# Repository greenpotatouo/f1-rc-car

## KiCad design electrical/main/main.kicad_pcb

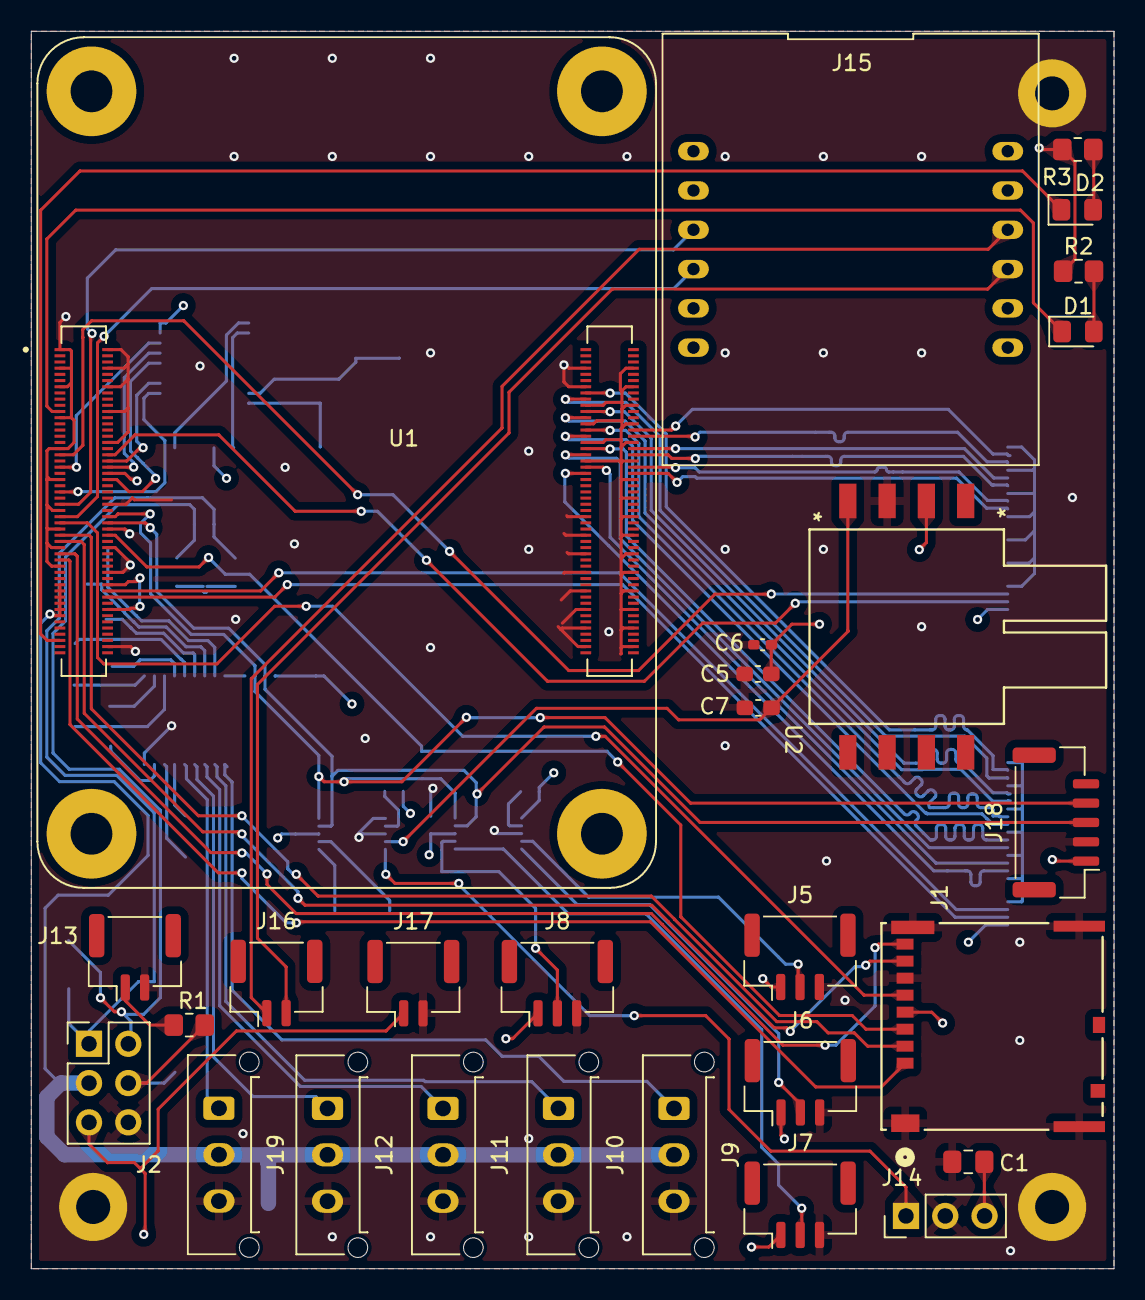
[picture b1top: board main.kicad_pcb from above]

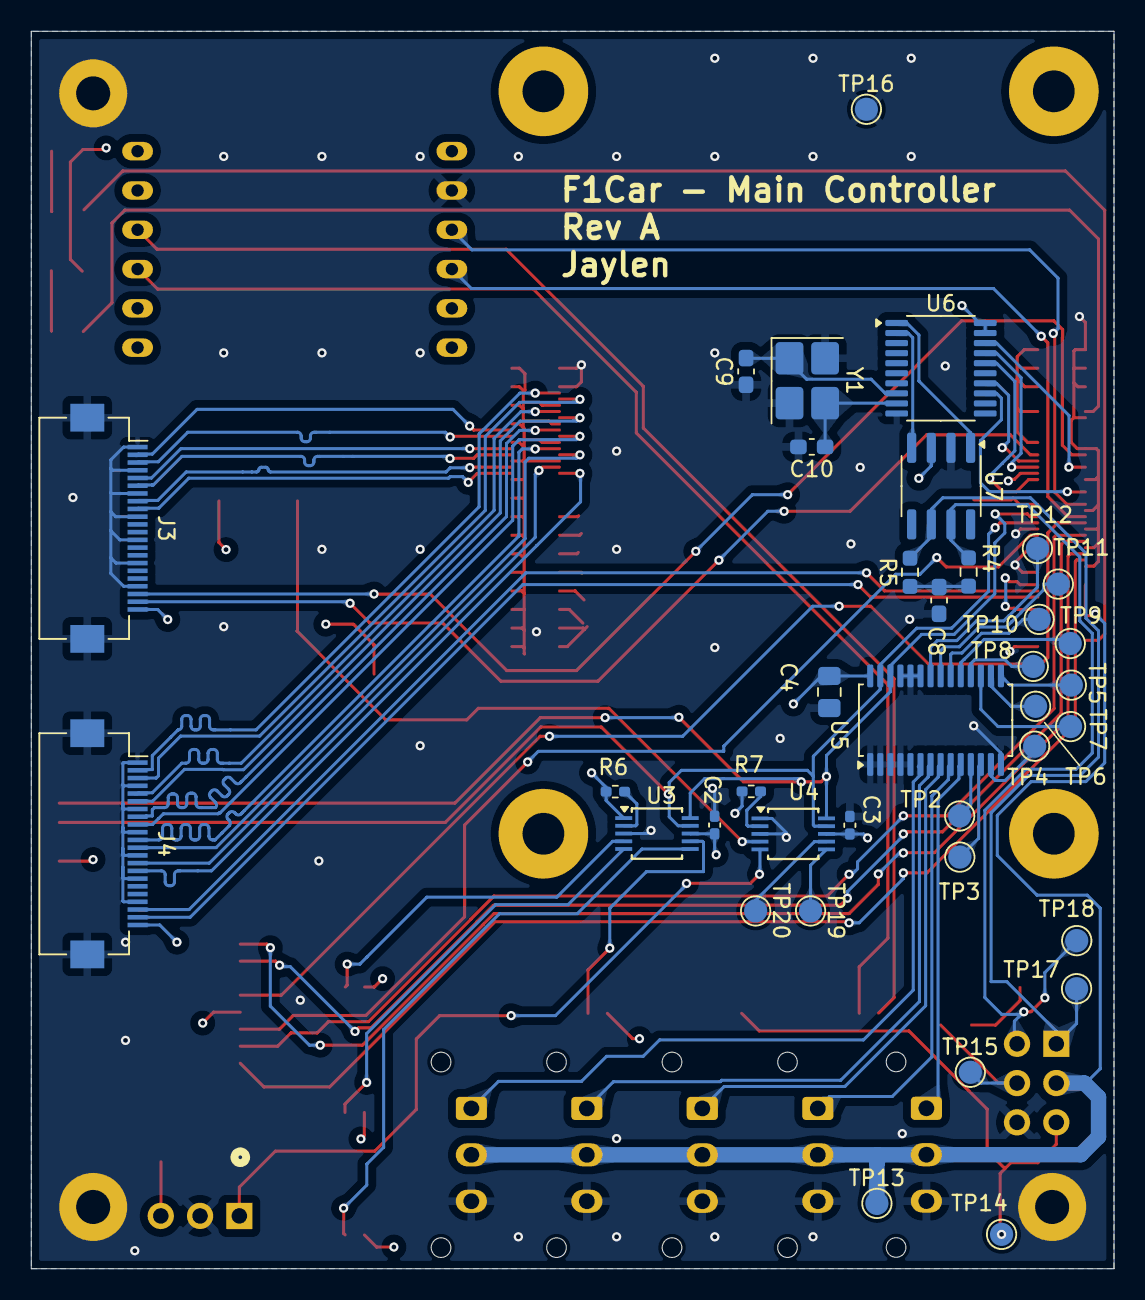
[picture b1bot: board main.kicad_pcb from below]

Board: 4 copper layers, 70.0 x 80.0 mm, 68 parts (37 on the bottom side), 80 nets.

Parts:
C1, C4: 10uF; C_0805_2012Metric_Pad1.18x1.45mm_HandSolder
C2, C3: 100nF; C_0402_1005Metric_Pad0.74x0.62mm_HandSolder
C5: 10nF; C_0603_1608Metric_Pad1.08x0.95mm_HandSolder
C6: 1uF; C_0402_1005Metric_Pad0.74x0.62mm_HandSolder
C7: 470pF; C_0603_1608Metric_Pad1.08x0.95mm_HandSolder
C8: 4.7nF; C_0603_1608Metric_Pad1.08x0.95mm_HandSolder
C9, C10: 22pF; C_0603_1608Metric_Pad1.08x0.95mm_HandSolder
D1, D2: LED; LED_0805_2012Metric_Pad1.15x1.40mm_HandSolder
H1, H2, H3: MountingHole_Pad; MountingHole_2.2mm_M2_Pad
J1: Micro_SD_Card_Det2; Molex-503398-1892
J2: Board-to-board; PinHeader_2x03_P2.54mm_Vertical
J3: CAM0; Hirose_FH12-22S-0.5SH_1x22-1MP_P0.50mm_Horizontal
J4: CAM1; Hirose_FH12-22S-0.5SH_1x22-1MP_P0.50mm_Horizontal
J5: ENCODER0; JST_GH_BM03B-GHS-TBT_1x03-1MP_P1.25mm_Vertical
J6: ENCODER1; JST_GH_BM03B-GHS-TBT_1x03-1MP_P1.25mm_Vertical
J7: ENCODER2; JST_GH_BM03B-GHS-TBT_1x03-1MP_P1.25mm_Vertical
J8: ENCODER3; JST_GH_BM03B-GHS-TBT_1x03-1MP_P1.25mm_Vertical
J9: SERVO0; Molex_Micro-Fit_3.0_43650-0315_1x03_P3.00mm_Vertical
J10: SERVO1; Molex_Micro-Fit_3.0_43650-0315_1x03_P3.00mm_Vertical
J11: SERVO2; Molex_Micro-Fit_3.0_43650-0315_1x03_P3.00mm_Vertical
J12: SERVO3; Molex_Micro-Fit_3.0_43650-0315_1x03_P3.00mm_Vertical
J13: LED1; JST_GH_BM02B-GHS-TBT_1x02-1MP_P1.25mm_Vertical
J14: MIC; PinHeader_1x03_P2.54mm_Vertical
J15: AMP; dfplayer-pro
J16: SPEAKER; JST_GH_BM02B-GHS-TBT_1x02-1MP_P1.25mm_Vertical
J17: FAN0; JST_GH_BM02B-GHS-TBT_1x02-1MP_P1.25mm_Vertical
J18: IMU; JST_GH_BM05B-GHS-TBT_1x05-1MP_P1.25mm_Vertical
J19: SERVO4; Molex_Micro-Fit_3.0_43650-0315_1x03_P3.00mm_Vertical
R1: R; R_0805_2012Metric_Pad1.20x1.40mm_HandSolder
R2, R3: 330; R_0805_2012Metric_Pad1.20x1.40mm_HandSolder
R4, R5: 60.4; R_0603_1608Metric_Pad0.98x0.95mm_HandSolder
R6, R7: 10k; R_0402_1005Metric_Pad0.72x0.64mm_HandSolder
TP2, TP3, TP4, TP5, TP6, TP7, TP8, TP9, TP10, TP11, TP12, TP13, TP14, TP15, TP16, TP17, TP18, TP19, TP20: TestPoint; TestPoint_Pad_D1.5mm
U1: SC0671
U2: MP3V5010DP
U3, U4: ADS1115IDGS; TSSOP-10_3x3mm_P0.5mm
U5: PCA9685PW; TSSOP-28_4.4x9.7mm_P0.65mm
U6: MCP2515-xST; TSSOP-20_4.4x6.5mm_P0.65mm
U7: SN65HVD232; SOIC-8_3.9x4.9mm_P1.27mm
Y1: Crystal_GND24; Crystal_SMD_3225-4Pin_3.2x2.5mm_HandSoldering

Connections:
3V3: C1.1, C2.1, C3.1, C4.1, C5.1, C6.1, J1.4 (VDD), J2.4, J3.22, J4.22, J5.1, J6.1, J7.1, J8.1, J14.3, J15.1, J18.1, R1.1, R2.2, R3.2, R6.2, R7.2, TP15.1, U2.2 (VS), U3.1 (ADDR), U3.8 (VDD), U4.8 (VDD), U5.28 (VDD), U6.19 (~RESET), U6.20 (VDD), U7.3 (VCC)
5V: J2.3, J9.2, J10.2, J11.2, J12.2, J19.2, TP13.1, U1.77 (+5V(INPUT)), U1.79 (+5V(INPUT)__1), U1.81 (+5V(INPUT)__2), U1.83 (+5V(INPUT)__3), U1.85 (+5V(INPUT)__4), U1.87 (+5V(INPUT)__5)
12V: J2.5, J17.1, TP14.1
ACTIVITY_LED: D1.1 (K), U1.21 (PI_~LED_ACTIVITY)
AIRSPEED: C7.1, U2.4 (VOUT), U4.4 (AIN0)
AMP_RX: J15.3, U1.51 (GPIO15)
AMP_TX: J15.4, U1.55 (GPIO14)
CAM0_C_N: J3.8, U1.140 (CAM0_C_N)
CAM0_C_P: J3.9, U1.142 (CAM0_C_P)
CAM0_D0_N: J3.2, U1.128 (CAM0_D0_N)
CAM0_D0_P: J3.3, U1.130 (CAM0_D0_P)
CAM0_D1_N: J3.5, U1.134 (CAM0_D1_N)
CAM0_D1_P: J3.6, U1.136 (CAM0_D1_P)
CAM1_C_N: J4.8, U1.127 (CAM1_C_N)
CAM1_C_P: J4.9, U1.129 (CAM1_C_P)
CAM1_D0_N: J4.2, U1.115 (CAM1_D0_N)
CAM1_D0_P: J4.3, U1.117 (CAM1_D0_P)
CAM1_D1_N: J4.5, U1.121 (CAM1_D1_N)
CAM1_D1_P: J4.6, U1.123 (CAM1_D1_P)
CAM1_D2_N: J4.11, U1.133 (CAM1_D2_N)
CAM1_D2_P: J4.12, U1.135 (CAM1_D2_P)
CAM1_D3_N: J4.14, U1.139 (CAM1_D3_N)
CAM1_D3_P: J4.15, U1.141 (CAM1_D3_P)
CANH: J2.2, R4.1, TP18.1, U7.7 (CANH)
CANL: J2.1, R5.2, TP17.1, U7.6 (CANL)
CAN_CS: U1.39 (GPIO8), U6.18 (~CS)
CAN_INT: U1.47 (GPIO23), U6.13 (~INT)
CAN_RX: U6.2 (RXCAN), U7.4 (R)
CAN_TX: U6.1 (TXCAN), U7.1 (D)
ENCODER0: J5.2, U3.4 (AIN0)
ENCODER1: J6.2, U3.5 (AIN1)
ENCODER2: J7.2, U3.6 (AIN2)
ENCODER3: J8.2, U3.7 (AIN3)
GND: C1.2, C2.2, C3.2, C4.2, C5.2, C6.2, C7.2, C8.2, C9.1, C10.2, H1.1, H2.1, H3.1, J1.6 (VSS), J1.11 (SHIELD), J2.6, J3.1, J3.4, J3.7, J3.10, J3.13, J3.16, J3.19, J3.MP (Pin_22), J4.1, J4.4, J4.7, J4.10, J4.13, J4.16, J4.19, J4.MP (Pin_22), J5.3, J6.3, J7.3, J8.3, J9.3, J10.3, J11.3, J12.3, J13.2, J14.2, J15.2, J17.2, J18.2, J19.3, TP16.1, U1.1 (GND), U1.2 (GND__1), U1.7 (GND__2), U1.8 (GND__3), U1.13 (GND__4), U1.14 (GND__5), U1.22 (GND__6), U1.23 (GND__7), U1.32 (GND__8), U1.33 (GND__9), U1.42 (GND__10), U1.43 (GND__11), U1.52 (GND__12), U1.53 (GND__13), U1.59 (GND__14), U1.60 (GND__15), U1.65 (GND__16), U1.66 (GND__17), U1.71 (GND__18), U1.74 (GND__19), U1.98 (GND__20), U1.107 (GND__21), U1.108 (GND__22), U1.113 (GND__23), U1.114 (GND__24), U1.119 (GND__25), U1.120 (GND__26), U1.125 (GND__27), U1.126 (GND__28), U1.131 (GND__29), U1.132 (GND__30), U1.137 (GND__31), U1.138 (GND__32), U1.144 (GND__33), U1.150 (GND__34), U1.155 (GND__35), U1.156 (GND__36), U1.161 (GND__37), U1.162 (GND__38), U1.167 (GND__39), U1.168 (GND__40), U1.173 (GND__41), U1.174 (GND__42), U1.179 (GND__43), U1.180 (GND__44), U1.185 (GND__45), U1.186 (GND__46), U1.191 (GND__47), U1.192 (GND__48), U1.197 (GND__49), U1.198 (GND__50), U2.3 (GND), U3.3 (GND), U4.1 (ADDR), U4.3 (GND), U5.1 (A0), U5.2 (A1), U5.3 (A2), U5.4 (A3), U5.5 (A4), U5.14 (VSS), U5.23 (~OE), U5.24 (A5), U5.25 (EXTCLK), U6.10 (VSS), U7.2 (GND), Y1.2, Y1.4
MIC: J14.1, U4.5 (AIN1)
unnamed: C8.1, R4.2, R5.1
unnamed: D1.2 (A), R2.1
unnamed: D2.2 (A), R3.1
unnamed: J13.1, R1.2
unnamed: U1.78 (GPIO_VREF), U1.86 (CM4_3.3V(OUTPUT)__1)
unnamed: R6.1, U3.2 (ALERT/RDY)
unnamed: TP19.1, U4.6 (AIN2)
unnamed: TP20.1, U4.7 (AIN3)
unnamed: R7.1, U4.2 (ALERT/RDY)
unnamed: TP2.1, U5.11 (LED5)
unnamed: TP3.1, U5.12 (LED6)
unnamed: TP4.1, U5.13 (LED7)
unnamed: TP5.1, U5.15 (LED8)
unnamed: TP6.1, U5.16 (LED9)
unnamed: TP7.1, U5.17 (LED10)
unnamed: TP8.1, U5.18 (LED11)
unnamed: TP9.1, U5.19 (LED12)
unnamed: TP10.1, U5.20 (LED13)
unnamed: TP11.1, U5.21 (LED14)
unnamed: TP12.1, U5.22 (LED15)
OSC_H: C10.1, U6.9 (OSC1), Y1.3
OSC_L: C9.2, U6.8 (OSC2), Y1.1
PWR_LED: D2.1 (K), U1.95 (PI_LED_~PWR)
SCL0: J4.20, U1.80 (SCL0)
SCL1: J3.20, U1.35 (ID_SC)
SCL2: J18.4, U1.56 (GPIO3), U3.10 (SCL), U4.10 (SCL), U5.26 (SCL)
SDA0: J4.21, U1.82 (SDA0)
SDA1: J3.21, U1.36 (ID_SD)
SDA2: J18.3, U1.58 (GPIO2), U3.9 (SDA), U4.9 (SDA), U5.27 (SDA)
SD_CLK: J1.5 (CLK), U1.57 (SD_CLK)
SD_CMD: J1.3 (CMD), U1.62 (SD_CMD)
SD_DAT0: J1.7 (DAT0), U1.63 (SD_DAT0)
SD_DAT1: J1.8 (DAT1), U1.67 (SD_DAT1)
SD_DAT2: J1.1 (DAT2), U1.69 (SD_DAT2)
SD_DAT3: J1.2 (DAT3/CD), U1.61 (SD_DAT3)
SERVO0: J9.1, U5.6 (LED0)
SERVO1: J10.1, U5.7 (LED1)
SERVO2: J11.1, U5.8 (LED2)
SERVO3: J12.1, U5.9 (LED3)
SERVO4: J19.1, U5.10 (LED4)
SPEAKER+: J15.9, J16.2
SPEAKER-: J15.10, J16.1
SPI_MISO: U1.40 (GPIO9), U6.17 (SO)
SPI_MOSI: U1.44 (GPIO10), U6.16 (SI)
SPI_SCK: U1.38 (GPIO11), U6.14 (SCK)

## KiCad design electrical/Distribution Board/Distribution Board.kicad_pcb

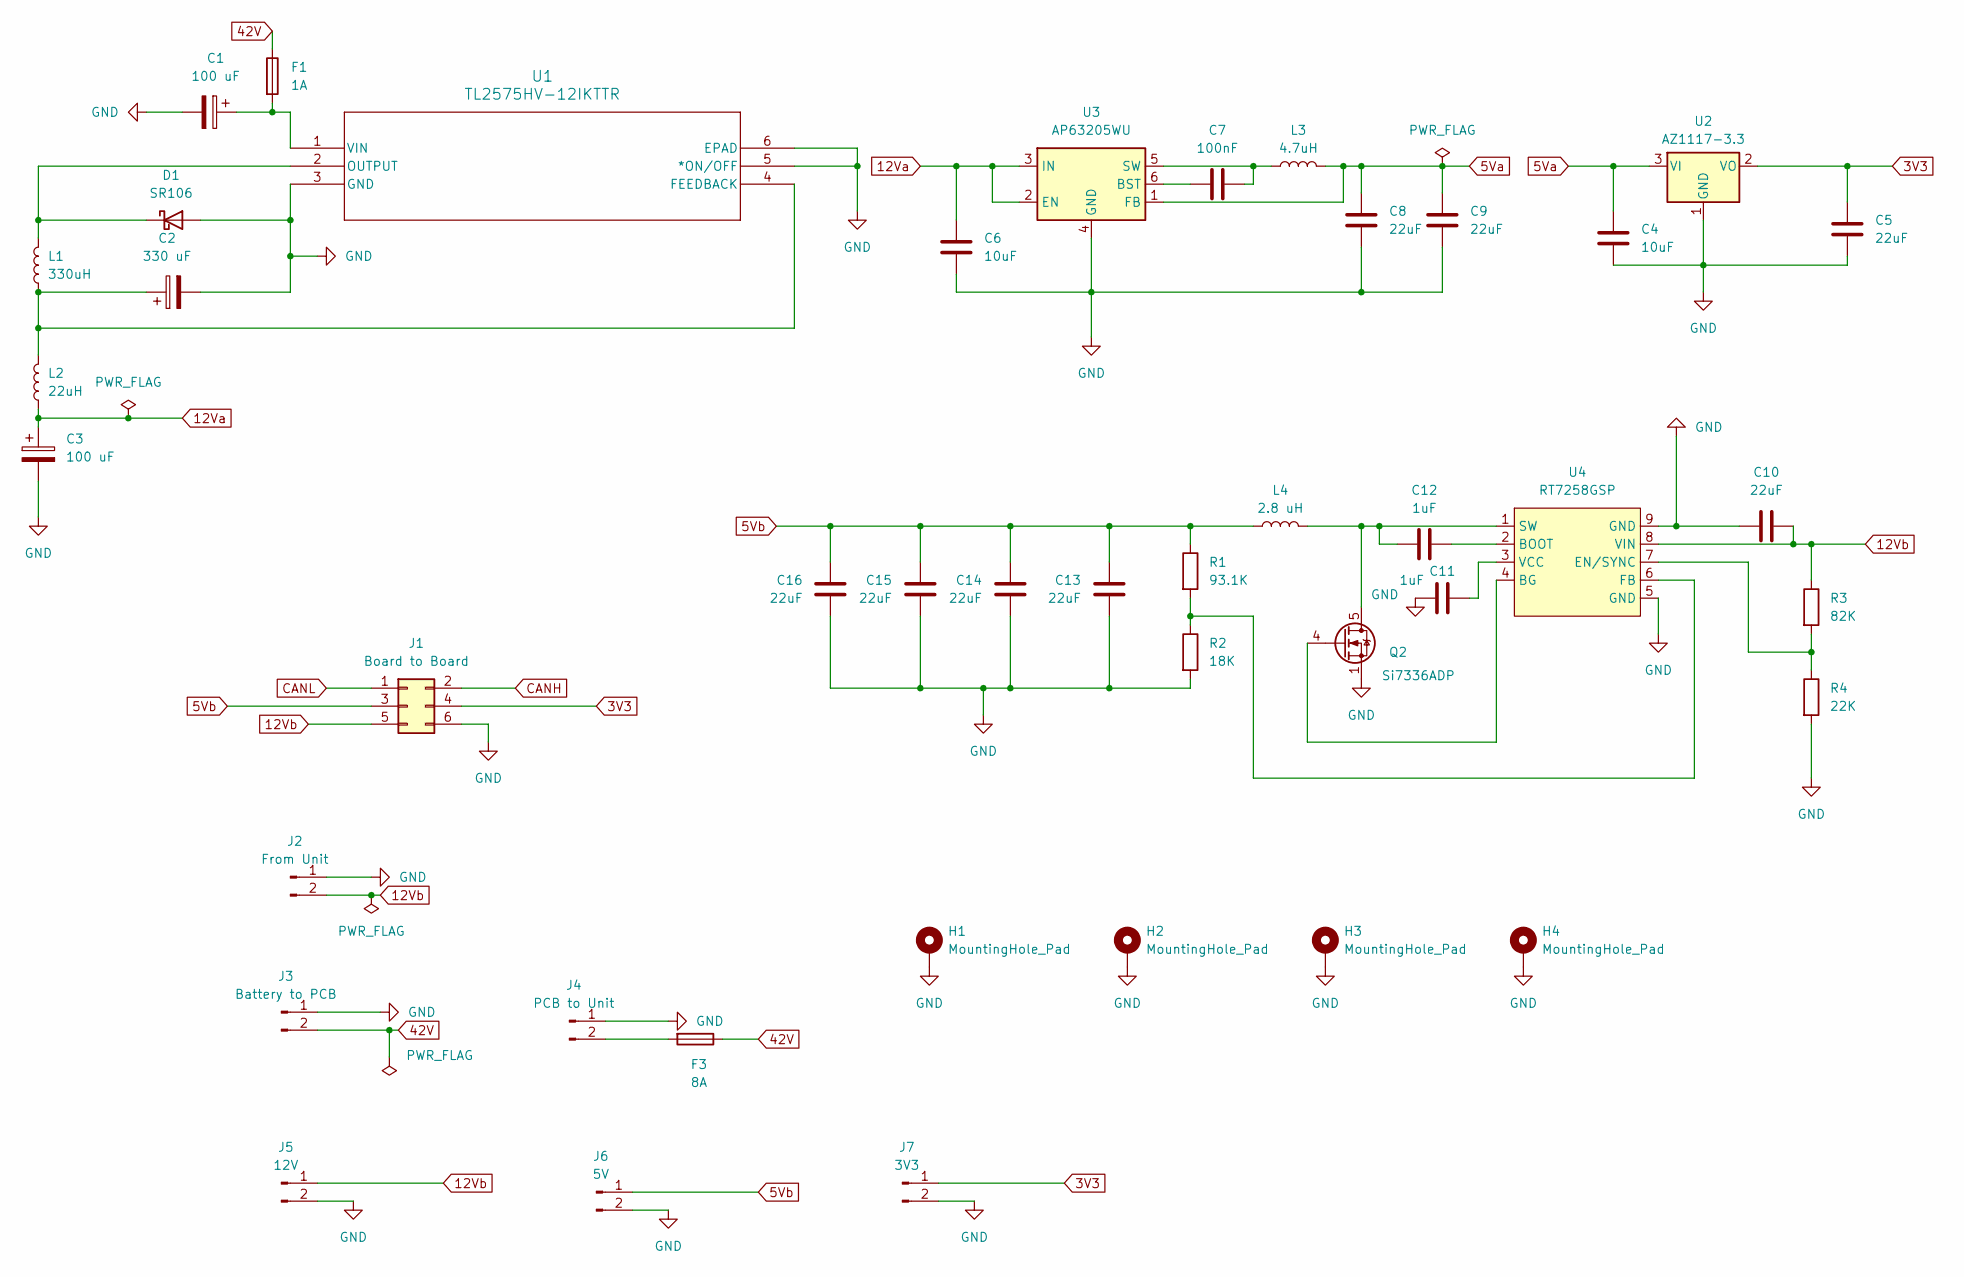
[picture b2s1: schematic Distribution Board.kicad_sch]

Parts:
C1, C3: 100 uF; CP_Elec_8x10.5
C2: 330 uF; CP_Elec_10x10
C4, C6: 10uF; C_0805_2012Metric_Pad1.18x1.45mm_HandSolder
C5, C8, C9, C10, C13, C14, C15, C16: 22uF; C_1206_3216Metric_Pad1.33x1.80mm_HandSolder
C7: 100nF; C_0402_1005Metric_Pad0.74x0.62mm_HandSolder
C11, C12: 1uF; C_0402_1005Metric_Pad0.74x0.62mm_HandSolder
D1: SR106; D_A-405_P7.62mm_Horizontal
F1: 1A; Fuse_1206_3216Metric
F3: 8A; Fuse_2512_6332Metric
H1, H2, H3, H4: MountingHole_Pad; MountingHole_2.2mm_M2_Pad
J1: Board to Board; PinHeader_2x03_P2.54mm_Vertical
J2: From Unit; AMASS_XT60PW-F_1x02_P7.20mm_Horizontal
J3: Battery to PCB; AMASS_XT60PW-F_1x02_P7.20mm_Horizontal
J4: PCB to Unit; AMASS_XT60PW-F_1x02_P7.20mm_Horizontal
J5: 12V; Molex_Micro-Fit_3.0_43650-0200_1x02_P3.00mm_Horizontal
J6: 5V; Molex_Micro-Fit_3.0_43650-0200_1x02_P3.00mm_Horizontal
J7: 3V3; Molex_Micro-Fit_3.0_43650-0200_1x02_P3.00mm_Horizontal
L1: 330uH; L_TaiTech_TMPC1265_13.5x12.5mm
L2: 22uH; L_Sumida_CDMC6D28_7.25x6.5mm
L3: 4.7uH; L_1008_2520Metric_Pad1.43x2.20mm_HandSolder
L4: 2.8 uH; L_Wuerth_HCI-1365
Q2: Si7336ADP; Vishay_PowerPAK_1212-8_Single
R1: 93.1K; R_0402_1005Metric_Pad0.72x0.64mm_HandSolder
R2: 18K; R_0402_1005Metric_Pad0.72x0.64mm_HandSolder
R3: 82K; R_0402_1005Metric_Pad0.72x0.64mm_HandSolder
R4: 22K; R_0402_1005Metric_Pad0.72x0.64mm_HandSolder
U1: TL2575HV-12IKTTR; KTT5_6P22X6P86-L
U2: AZ1117-3.3; SOT-89-3_Handsoldering
U3: AP63205WU; TSOT-23-6
U4: RT7258GSP; Texas_HTSOP-8-1EP_3.9x4.9mm_P1.27mm_EP2.95x4.9mm_Mask2.4x3.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

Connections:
3V3: C5.1, J1.4, J7.1, U2.2 (VO)
5Va: C4.1, C8.1, C9.1, L3.2, U2.3 (VI), U3.1 (FB)
5Vb: C13.1, C14.1, C15.1, C16.1, J1.3, J6.1, L4.1, R1.1
12Va: C3.1, C6.1, L2.1, U3.2 (EN), U3.3 (IN)
12Vb: C10.2, J1.5, J2.2, J5.1, R3.1, U4.8 (VIN)
42V: F1.1, F3.1, J3.2
CANH: J1.2
CANL: J1.1
GND: C1.2, C2.2, C3.2, C4.2, C5.2, C6.2, C8.2, C9.2, C10.1, C11.2, C13.2, C14.2, C15.2, C16.2, D1.2 (A), H1.1, H2.1, H3.1, H4.1, J1.6, J2.1, J3.1, J4.1, J5.2, J6.2, J7.2, Q2.1 (S), Q2.2 (S), Q2.3 (S), R2.2, R4.2, U1.3 (GND), U1.5 (*ON/OFF), U1.6 (EPAD), U2.1 (GND), U3.4 (GND), U4.5 (GND), U4.9 (GND)
unnamed: D1.1 (K), L1.2, U1.2 (OUTPUT)
unnamed: F3.2, J4.2
unnamed: C12.1, L4.2, Q2.5 (D), U4.1 (SW)
unnamed: Q2.4 (G), U4.4 (BG)
unnamed: C2.1, L1.1, L2.2, U1.4 (FEEDBACK)
unnamed: C1.1, F1.2, U1.1 (VIN)
unnamed: C7.2, U3.6 (BST)
unnamed: C7.1, L3.1, U3.5 (SW)
unnamed: C12.2, U4.2 (BOOT)
unnamed: R3.2, R4.1, U4.7 (EN/SYNC)
unnamed: R1.2, R2.1, U4.6 (FB)
unnamed: C11.1, U4.3 (VCC)

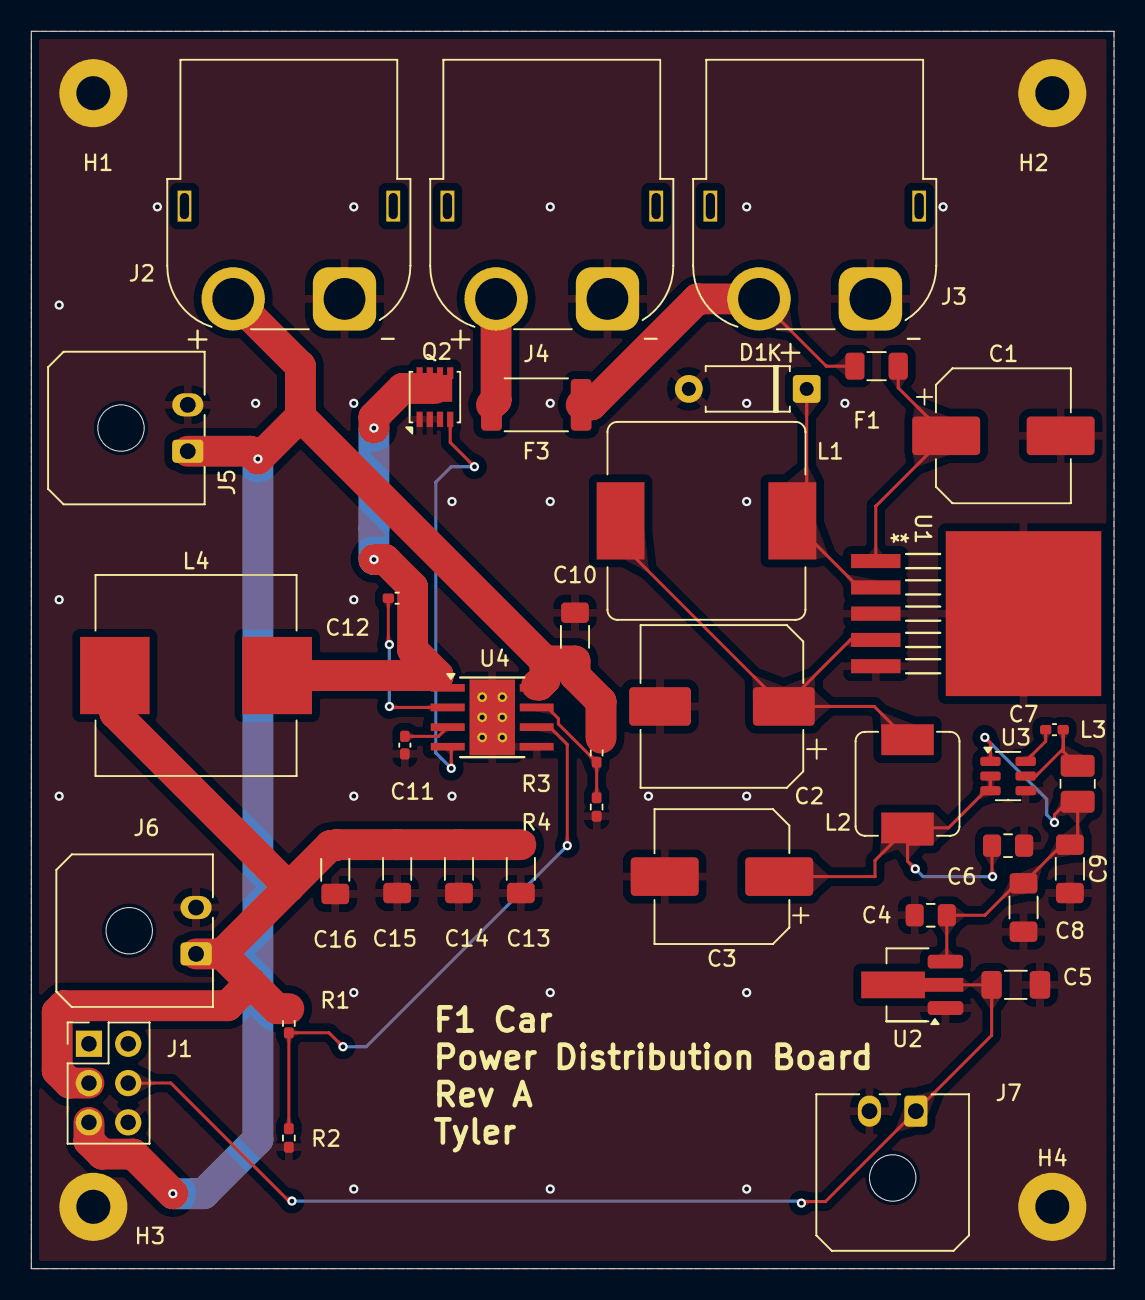
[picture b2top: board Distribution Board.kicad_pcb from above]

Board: 2 copper layers, 70.0 x 80.0 mm, 43 parts (0 on the bottom side), 19 nets.

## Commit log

2025-08-24 first commit
    - suspension WIP
    - car body WIP
    - steering WIP
    - wheel assembly
    - BMS
2025-08-24 fixed component linking in asssemblies
2025-08-27 underbody
2025-08-28 add manufacturing files, add updated schematics
2025-09-04 engine pcb files
2025-09-23 added transmission cad
2025-09-23 added transmission cad properly
2025-09-23 added engine cad
2025-09-23 added distribution board
2025-09-23 added main cm4 pcb files
2025-09-23 added battery cad
2026-01-08 testing ssh
